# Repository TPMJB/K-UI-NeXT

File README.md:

# K-UI native VMU checkpoint: 74958b387827

This is a preservation checkpoint on `checkpoint/native-vmu-20261024` in
`TPMJB/K-UI-NeXT`. It preserves the exact source tree and all 36 original
source commits through `74958b3878279fc916199a7cd330f7f17b036138`, matching
compiled builds, generated test evidence, and the recovered EDF reference.
The checkpoint container is a separate Git commit; its own SHA is not the
original source SHA. This checkpoint does not merge changes into `main`.

## Compiled builds

- [Latest Background fallback limit, 74958b387827](builds/K-UI-Native-Background-Bounds-74958b387827.zip?raw=true).
- [Previous Standard and Background comparison build, 9fa65fc1cae0](builds/K-UI-VMU-Retry-9fa65fc1cae0.zip?raw=true).

The latest candidate retains background DMA and limits synchronous PIO fallback
to one SD data block per native loader call or reader interrupt. Tests
reproduced the previous whole-request masked-work defect and verified bounded
fallback, byte-exact completion, CRC recovery, guest DMA ownership and unchanged
DMA-only scheduling sequences. The linked memory and stack checks pass without
relaxing boundaries. These results do not establish a console performance fix.

The prior test reported smooth Evolution 2 FMVs with Background, with occasional
gameplay stalls. The latest report after the 74958b387827 candidate likewise
says FMVs remain fine but gameplay hangs remain. The build association follows
the delivery/test sequence; no runtime build screen was supplied with that
report. The gameplay performance problem is still open. See `HARDWARE-TESTS.json`.
The prior build is preserved for direct comparison. The user's earlier
flawless EDF FMV report used **regular Standard loading**, not Background.
The original regular-loading performance difference remains unresolved.

Follow the README inside the selected build ZIP to personalize its loader with
an existing prepared card profile. The latest package requires Background On;
it does not add a new in-game mode switch. Virtual A2 and physical A1 passthrough
remain included. This recovery script is not a device installer.

## Exact source recovery

Clone this checkpoint branch and run the following from this folder:

```sh
python3 restore.py
```

The script validates all preserved files and part hashes, reconstructs the
base history bundle and exact historical EDF source archive, imports the
retained main prerequisite and original source bundles, then checks out the
exact latest source in `restored-source`. It refuses to replace an existing
source directory. The original source tree, 36-commit count and Git object
integrity are checked after recovery.

The main prerequisite `194a94483132c8dd30b0a21d7c20887c0e1eaed3` is retained as
the checkpoint container's parent, keeping shared Git objects reachable. The
base compact bundle preserves the exact prior 35 source commits. The small
incremental bundle adds the original latest commit without recreating authors,
dates or commit IDs.

Latest source tree: `0640a3f8bf9cc53dd8701ee751af95e936491867`.
All payload identities and file hashes are recorded in `checkpoint.json`.
The large standalone Full ZIPs are not duplicated here: their unique source,
history and historical reference payloads are preserved directly instead.

## Historical reference and audits

`reference/edf20f0f11a3` preserves the exact recovered EDF module and source
archive. Its corrected `provenance.json` explicitly records regular loading.
`provenance-original.json` is an unchanged archival record whose earlier
Background interpretation is superseded; its payload identities remain valid.

`audit/edf/EDF-STANDARD-BINARY-AUDIT.md` describes the exact historical Standard
reconstruction and comparisons. The supplied corpus image's raw2352 format
does not establish which image variant was launched in either console test.
The safe reconstructed Standard ELF/bin/map are inspection evidence, not a
replacement loader package. Unsafe SCEV experiment executables are excluded.

`audit/background-bounds` records the reproduced defect, regression cases and
final linked checks. The work limit bounds PIO data blocks, not elapsed time;
legacy command/token/recovery waits remain. Preserved DMA-only scheduling does
not establish movie performance when a read itself falls back to PIO.

No user VMU image, save file, disk ownership profile, retail game executable or
game track is included. Original game files were used read-only for analysis
outside this checkpoint.

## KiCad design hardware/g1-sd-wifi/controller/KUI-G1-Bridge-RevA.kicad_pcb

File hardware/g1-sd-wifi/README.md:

# K-UI G1 microSD and Wi-Fi bridge — Rev A

The design now has a complete native KiCad circuit, two routed CN503 flex arms, selected components and original FPGA logic. All 55 BASE SMT part types have catalog matches (two LCSC codes were taken from a search index and must be confirmed on lcsc.com with their JLC SMT entries: C112291 for the 220 Ω FPGA configuration resistor added on 17 October, and C59873 for the TPS62172 converters that replaced TPS62162 on 23 October), and candidate BOM/CPL files exist. **Prototype fabrication is not released yet:** carrier routing and electrical layout review, mechanical support/fit and assembler placement/fixture review remain open. Device timing and firmware qualification are also outstanding. This directory supersedes the historical MCU-only starter.

The Dreamcast VA1 keeps its original 3.3 V GD-ROM as device0. The bridge supplies ATA device1, raw microSD sectors and Wi-Fi transport. K-UI is the sole filesystem owner; the C5 never independently mounts the card. exFAT is the baseline user choice; ext4 remains a software option. No FAT32 setup is prescribed.

| Implemented hardware | Selected component or circuit |
| --- | --- |
| ATA front end | U10 LCMXO2-2000HC-4TG100C; 50 MHz clock, JTAG configured by the RP2350 (J10 pads as an alternative), TX/RX FIFOs and hardware isolation |
| Controller | U201 RP2350B with boot NOR, native four-bit SD, USB/SWD recovery, and FPGA JTAG/PROGRAMn control |
| Bridge cache | U203 APS6404L-3SQR-ZR, 8 MiB PSRAM on QMI CS1/GPIO47; does not add SH-4 system RAM |
| microSD | Molex1040310811 socket, card detect, pullups and rail-qualified bidirectional isolation |
| Wi-Fi | Manual USB-free XIAO ESP32-C5, sixteen Harwin spring contacts, switched5 V, isolated SPI/UART and EN/BOOT recovery |
| Power | Dedicated fused 5 V pair (reverse-blocked on the bench only; installed, the tap-end harness fuse is the reverse-polarity protection), separate TPS62172 logic/storage bucks, power warning, supervisors and DNP reserve bank |
| G1 attachment | Independent passive20-conductor A/B arms and Hirose FH12 bottom-contact sockets; audio/+12 V excluded. The sockets must move before an order: arm B cannot reach J51 as placed |
| Optional BIOS | DNP x8 NOR, extra ROM taps, physical independent stock recovery and hardware-qualified write arm; active factory bank0 |

## Open the actual design

Open [the controller project](controller/KUI-G1-Bridge-RevA.kicad_pro) with KiCad10. The [root schematic](controller/KUI-G1-Bridge-RevA.kicad_sch) links eleven component sheets. The [carrier PCB](controller/KUI-G1-Bridge-RevA.kicad_pcb) is a draft with a BIOS clearance opening and an open CN503 notch. Both flex projects are under [flex/](flex/); A and B have different contact maps and are not interchangeable.

[Physical component contracts](design/blocks/) drive the deterministic schematic generator. Local symbol and footprint libraries are included. The [physical pad audit](design/physical-pad-audit.json) checks every electrical terminal against KiCad's loaded footprint, including exposed pads and connector anchors. [Controller notes](design/controller-implementation.md), [power/isolation notes](design/power-and-isolation.md) and [BIOS population notes](design/BIOS-variant.md) describe actual pins and circuits. [Current GPIO allocation](controller/K-UI-G1-GPIO-RevA.csv) is controller-to-FPGA/SD/C5, rather than the original direct-ATA candidate.

The reusable [integration checker](tools/check_integration.py) verifies the source contracts against the integrated native components and exported XML netlist, checks 100 FPGA package functions and 56 pin constraints, and evaluates 8,240 hardware safety combinations using the exported connections. From the repository root, run `python hardware/g1-sd-wifi/tools/check_integration.py --check`. After reviewed source changes and a fresh native netlist export, omit `--check` to refresh [integration-audit.json](design/integration-audit.json).

The [FPGA directory](fpga/) contains synthesizable logic, exact physical-pin LPF, simulation scoreboards and the MCU-link contract. Simulation and MachXO2 resource mapping pass. A Lattice device-fit/timing result and completed RP2350 ATA/media firmware are still required; there is no validated programming image or game-compatibility claim. Initial firmware must advertise PIO0 only. DMA ownership is provisioned and tested in simulation, but performance and physical timing are unqualified.

## Measured mechanical limits

One more console-open session is needed before the carrier or either flex arm is ordered: the unpowered CN503 row proof, the 1:1 fit check, the flex route survey and the shield-height check in [docs/OWNER-NEXT-STEPS.md](docs/OWNER-NEXT-STEPS.md) items 1, 3, 3a and 3b. Their results feed one more layout revision: the flex sockets J50/J51 must move, because arm B cannot reach J51 as placed. Motherboard-top clearance is6 mm in the BIOS/CN503/lower-shield region,8 mm elsewhere, and zero over the two thermal-contact chips. Nominal carrier underside is2.5 mm above the motherboard;0.8 mm PCB puts its top at3.3 mm. A2 mm FPC connector reaches5.3 mm before tolerances. The C5 assembly is reserved for the8 mm region and needs a supported0.90 mm contact gap and removable clamp.

BIOS body26.68 ×12.65 mm, outer lead span16.66 mm, height approximately2 mm. Its long axis is west-east; CN503's long axis is north-south. CN503 is38.67 mm long,6.56 mm maximum housing width; accepted solder-contact pitch is1.00 mm with approximately0.44 mm metal width. The25-contact measured run is24.39 mm. BIOS-to-connector housing distance is approximately12 mm; the west BIOS strip and east connector strip are approximately7 mm each. Those strips contain existing parts and solder joints. The housing-derived5.03 mm row spacing does not constrain the independent flex arms.

The 59 × 115 mm carrier envelope and cutout/notch north-south registration are provisional. The outline was 59 × 105 mm until 10 October 2026; it gained a 10 mm band between the FPGA area and the BIOS opening, so relative to the BIOS and CN503 the carrier now reaches 10 mm further north (toward the AV connector) and its south edge is unchanged. The angled photographs do not establish a production outline or support location. Existing tall capacitors, case features, thermal-pad pressure, C5 height/retention, SD access and shield insulation require mechanical review. No shield cutting is assumed. [Actual-size carrier fit sheets](mechanical/README.md) use native PCB edges and component pads, with Letter/A4 paper choices and independent horizontal/vertical calibration.

## Manufacture and review

[Manufacturing status](manufacturing/README.md) identifies the current order blockers, native checks, exact draft settings and procurement work. Final release uses three separate archives: rigid carrier, flexA and flexB. The exporter refuses to publish an order package while required checks, assembly data and reviewed source hashes are incomplete.

JLC's exact catalog pages require assembly support fixtures for both the **Harwin S7221-45R contacts (C22445132)** and **Abracon ASE-50.000MHZ-LC-T oscillator (C596955)**. Obtain assembler agreement on those fixtures before releasing an assembly order. The C5 retention clamp is a separate mechanical installation requirement. [The purchasing worksheet](manufacturing/parts-to-buy.csv) records the exact SMT identities and fixture notices.

The historical dispositions remain in [docs/](docs/); Claude's original reviews are pinned to [commit b207dd6](https://github.com/TPMJB/K-UI-NeXT/tree/b207dd659565826ffd757ccf7abe1998f63c9202/docs). The [implementation status](design/IMPLEMENTATION-STATUS-2026-10-10.md) maps each accepted addition to its circuit or source artifact and remaining condition. Software caching/OTA/BIOS programming, runtime bank switching and measured SD power-cut retention are subsequent implementation/qualification work; a DNP reserve capacitor footprint cannot establish safe write completion. The original controller starter is preserved under [controller/reference/](controller/reference/).

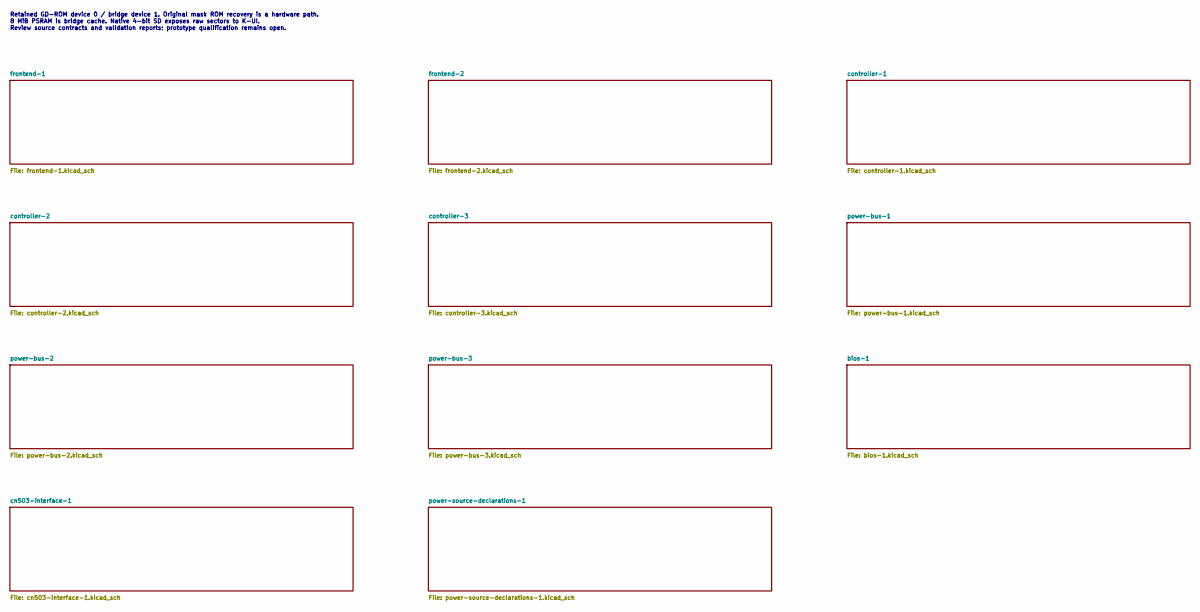
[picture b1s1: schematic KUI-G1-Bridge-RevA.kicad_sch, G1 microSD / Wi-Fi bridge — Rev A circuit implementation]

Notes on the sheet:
Retained GD-ROM device 0 / bridge device 1. Original mask ROM recovery is a hardware path. 8 MiB PSRAM is bridge cache. Native 4-bit SD exposes raw sectors to K-UI. Review source contracts and validation reports; prototype qualification remains open.

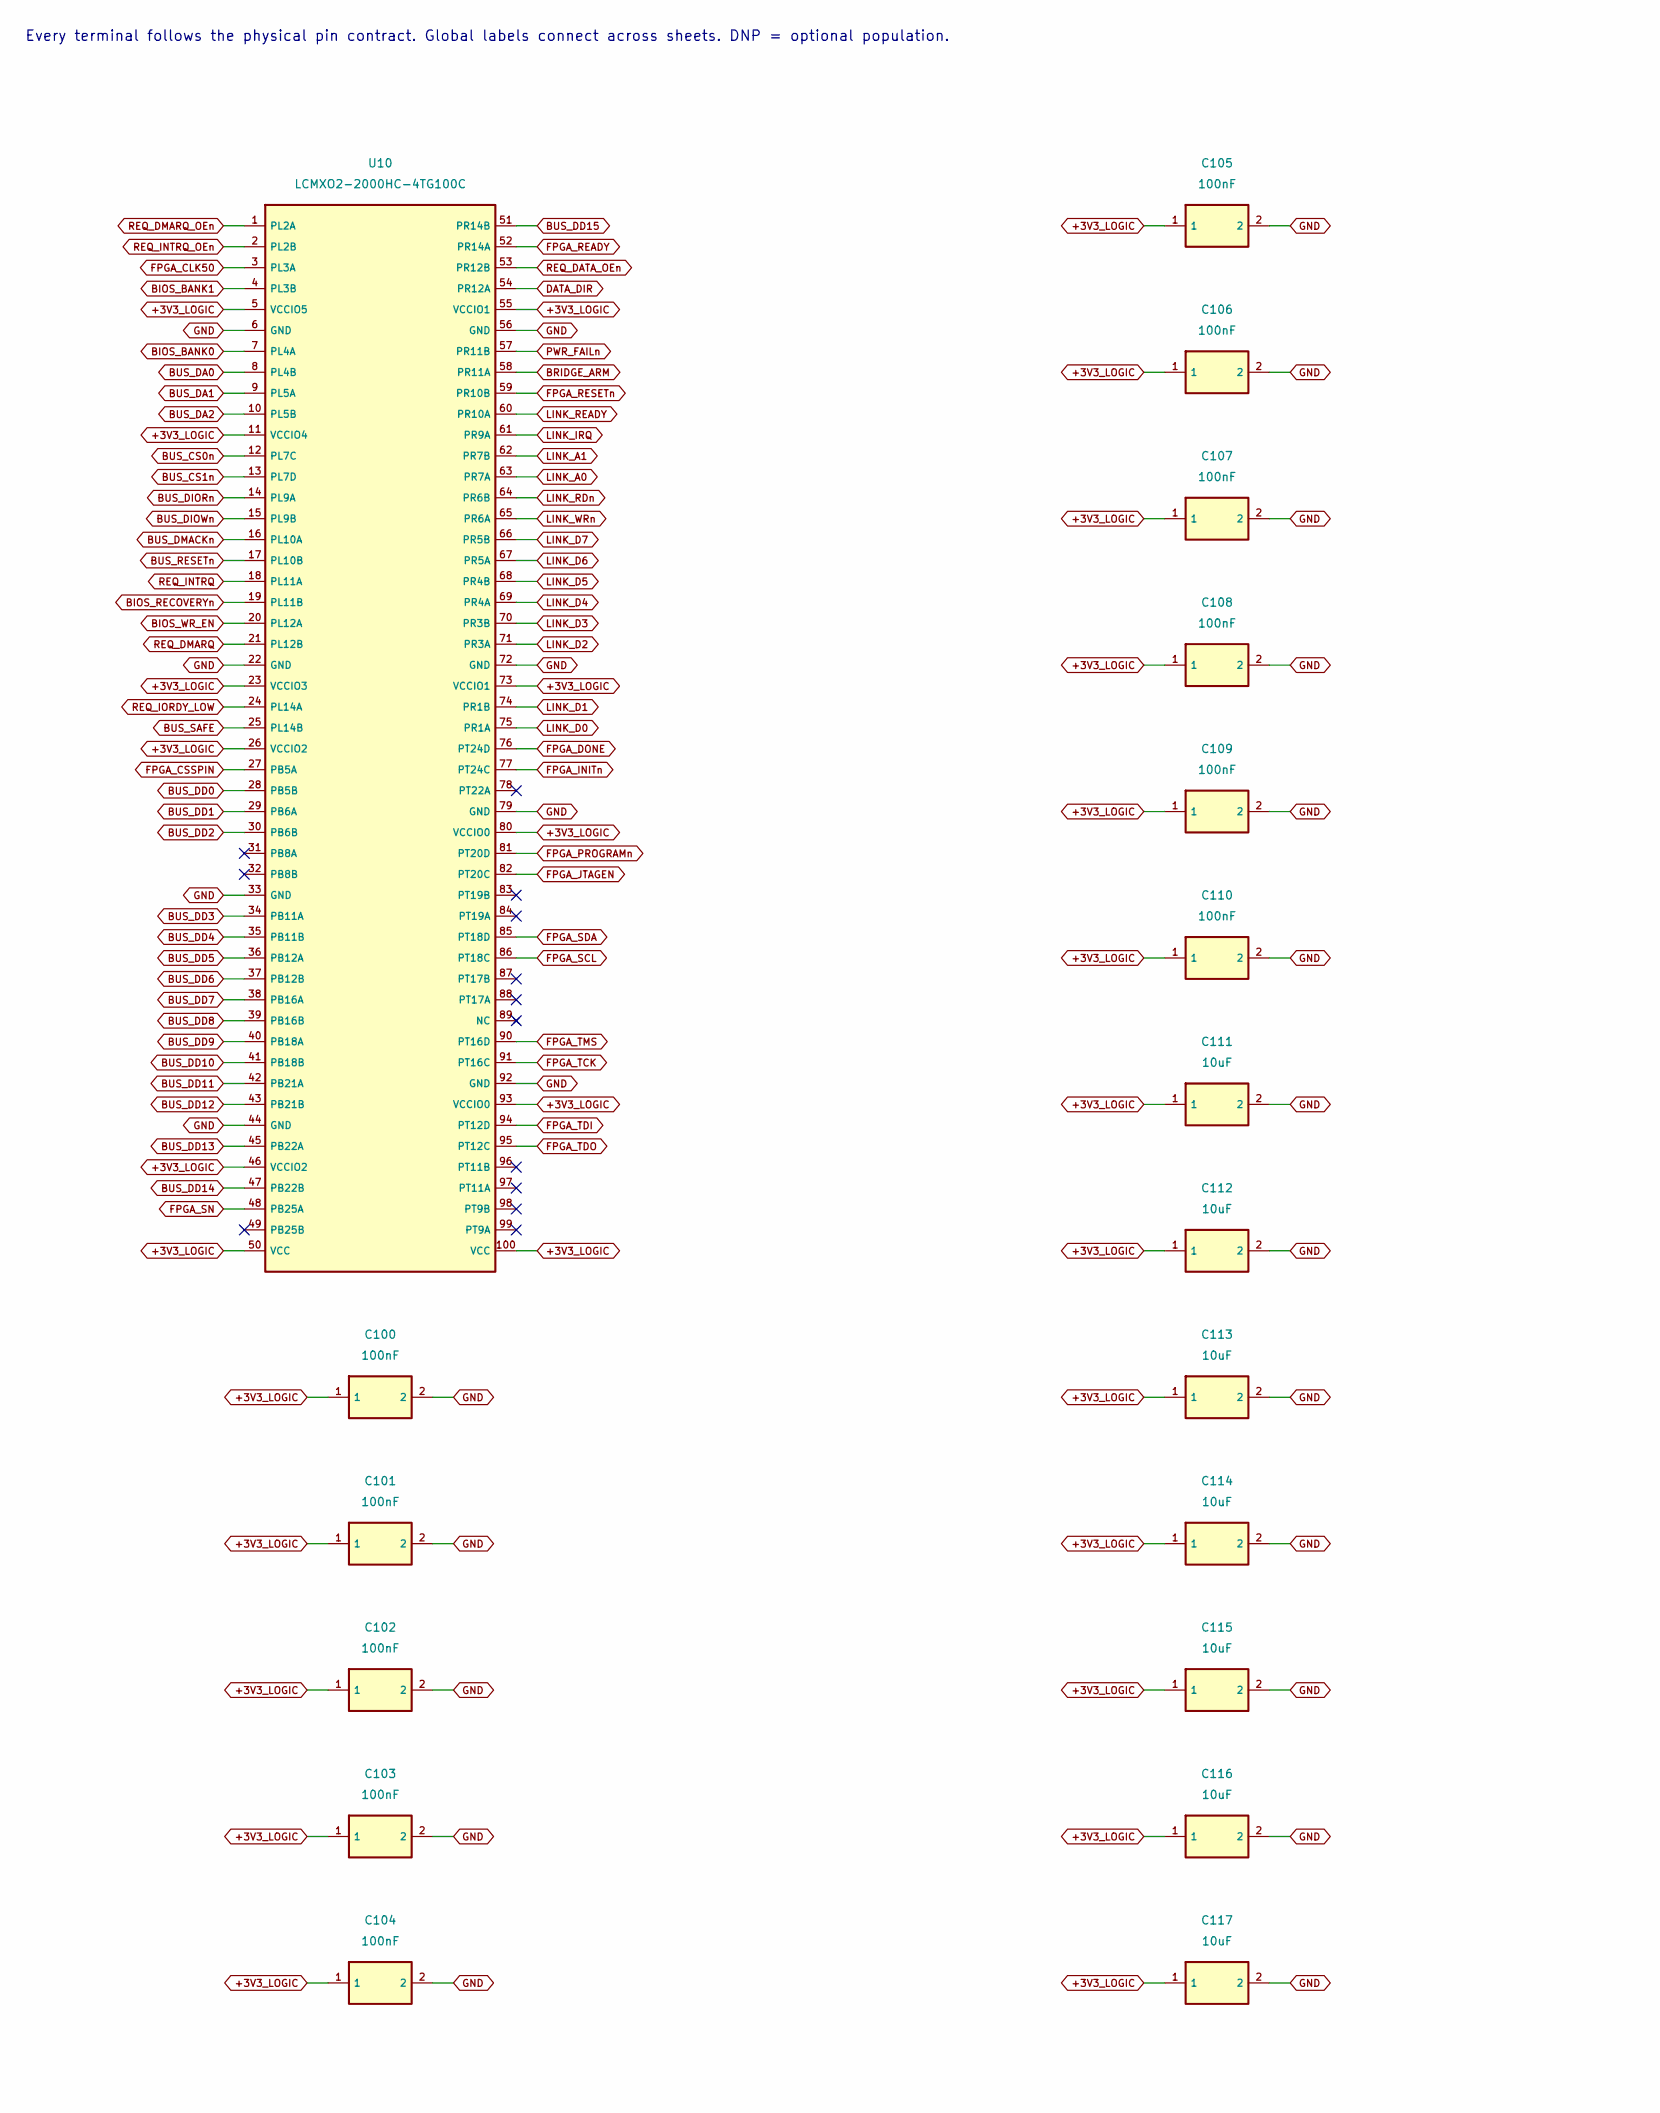
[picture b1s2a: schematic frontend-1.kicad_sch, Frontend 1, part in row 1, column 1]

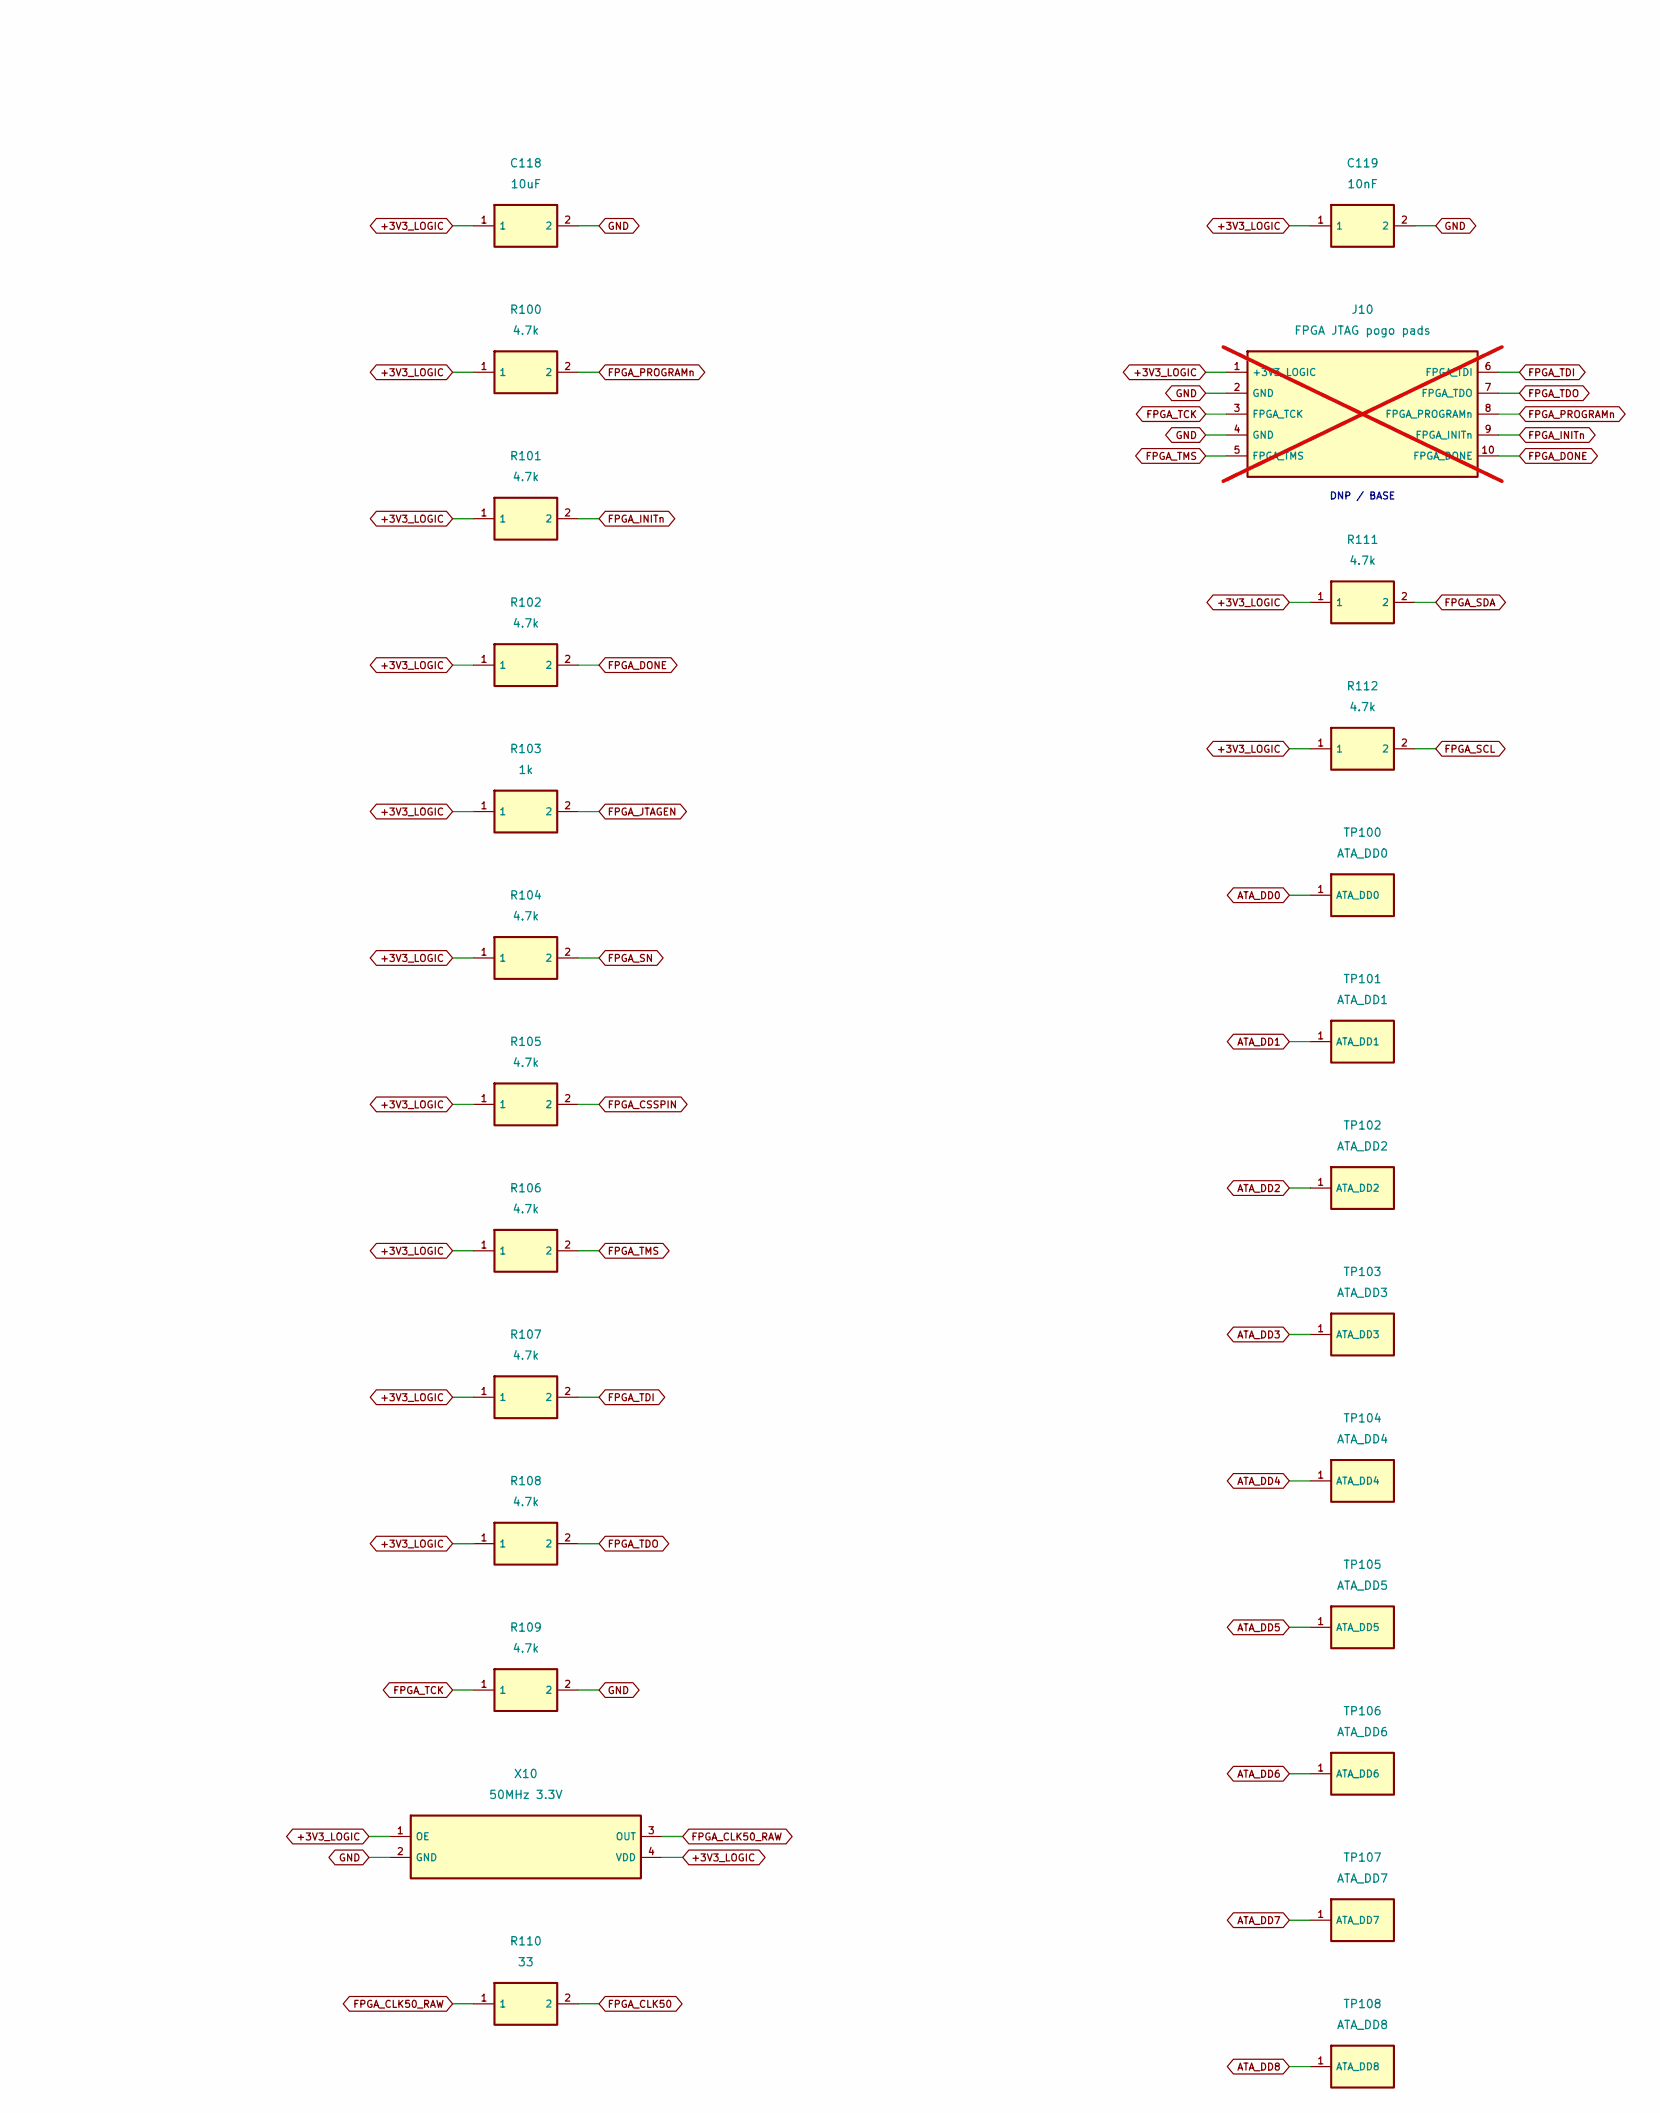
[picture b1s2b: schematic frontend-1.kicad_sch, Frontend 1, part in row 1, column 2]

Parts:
C100, C101, C102, C103, C104, C105, C106, C107, C108, C109, C110: 100nF; C_0402_1005Metric; MPN CL05B104KO5NNNC
C111, C112, C113, C114, C115, C116, C117, C118: 10uF; C_0603_1608Metric; MPN CL10A106MQ8NNNC
C119: 10nF; C_0402_1005Metric; MPN CL05B103KB5NNNC
J10: FPGA JTAG pogo pads; PinHeader_2x05_P1.27mm_Vertical; not fitted
R100, R101, R102, R104, R105, R106, R107, R108, R109, R111, R112: 4.7k; R_0402_1005Metric; MPN RC0402FR-074K7L
R103: 1k; R_0402_1005Metric; MPN RC0402FR-071KL
R110: 33; R_0402_1005Metric; MPN RC0402FR-0733RL
TP100: ATA_DD0; RawProbe_Pad_D1.0mm_NoPaste; MPN PCB_TEST_PAD
TP101: ATA_DD1; RawProbe_Pad_D1.0mm_NoPaste; MPN PCB_TEST_PAD
TP102: ATA_DD2; RawProbe_Pad_D1.0mm_NoPaste; MPN PCB_TEST_PAD
TP103: ATA_DD3; RawProbe_Pad_D1.0mm_NoPaste; MPN PCB_TEST_PAD
TP104: ATA_DD4; RawProbe_Pad_D1.0mm_NoPaste; MPN PCB_TEST_PAD
TP105: ATA_DD5; RawProbe_Pad_D1.0mm_NoPaste; MPN PCB_TEST_PAD
TP106: ATA_DD6; RawProbe_Pad_D1.0mm_NoPaste; MPN PCB_TEST_PAD
TP107: ATA_DD7; RawProbe_Pad_D1.0mm_NoPaste; MPN PCB_TEST_PAD
TP108: ATA_DD8; RawProbe_Pad_D1.0mm_NoPaste; MPN PCB_TEST_PAD
U10: LCMXO2-2000HC-4TG100C; TQFP-100_14x14mm_P0.5mm; MPN LCMXO2-2000HC-4TG100C; LCSC C1521632
X10: 50MHz 3.3V; Oscillator_SMD_Abracon_ASE-4Pin_3.2x2.5mm; MPN ASE-50.000MHZ-LC-T

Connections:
+3V3_LOGIC: C100.1, C101.1, C102.1, C103.1, C104.1, C105.1, C106.1, C107.1, C108.1, C109.1, C110.1, C111.1, C112.1, C113.1, C114.1, C115.1, C116.1, C117.1, C118.1, C119.1, J10.1 (+3V3_LOGIC), R100.1, R101.1, R102.1, R103.1, R104.1, R105.1, R106.1, R107.1, R108.1, R111.1, R112.1, U10.5 (VCCIO5), U10.11 (VCCIO4), U10.23 (VCCIO3), U10.26 (VCCIO2), U10.46 (VCCIO2), U10.50 (VCC), U10.55 (VCCIO1), U10.73 (VCCIO1), U10.80 (VCCIO0), U10.93 (VCCIO0), U10.100 (VCC), X10.1 (OE), X10.4 (VDD); also elsewhere on the board
ATA_DD0: TP100.1; also elsewhere on the board
ATA_DD1: TP101.1; also elsewhere on the board
ATA_DD2: TP102.1; also elsewhere on the board
ATA_DD3: TP103.1; also elsewhere on the board
ATA_DD4: TP104.1; also elsewhere on the board
ATA_DD5: TP105.1; also elsewhere on the board
ATA_DD6: TP106.1; also elsewhere on the board
ATA_DD7: TP107.1; also elsewhere on the board
ATA_DD8: TP108.1; also elsewhere on the board
BIOS_BANK0: U10.7 (PL4A); also elsewhere on the board
BIOS_BANK1: U10.4 (PL3B); also elsewhere on the board
BIOS_RECOVERYn: U10.19 (PL11B); also elsewhere on the board
BIOS_WR_EN: U10.20 (PL12A); also elsewhere on the board
BRIDGE_ARM: U10.58 (PR11A); also elsewhere on the board
BUS_CS0n: U10.12 (PL7C); also elsewhere on the board
BUS_CS1n: U10.13 (PL7D); also elsewhere on the board
BUS_DA0: U10.8 (PL4B); also elsewhere on the board
BUS_DA1: U10.9 (PL5A); also elsewhere on the board
BUS_DA2: U10.10 (PL5B); also elsewhere on the board
BUS_DD0: U10.28 (PB5B); also elsewhere on the board
BUS_DD1: U10.29 (PB6A); also elsewhere on the board
BUS_DD2: U10.30 (PB6B); also elsewhere on the board
BUS_DD3: U10.34 (PB11A); also elsewhere on the board
BUS_DD4: U10.35 (PB11B); also elsewhere on the board
BUS_DD5: U10.36 (PB12A); also elsewhere on the board
BUS_DD6: U10.37 (PB12B); also elsewhere on the board
BUS_DD7: U10.38 (PB16A); also elsewhere on the board
BUS_DD8: U10.39 (PB16B); also elsewhere on the board
BUS_DD9: U10.40 (PB18A); also elsewhere on the board
BUS_DD10: U10.41 (PB18B); also elsewhere on the board
BUS_DD11: U10.42 (PB21A); also elsewhere on the board
BUS_DD12: U10.43 (PB21B); also elsewhere on the board
BUS_DD13: U10.45 (PB22A); also elsewhere on the board
BUS_DD14: U10.47 (PB22B); also elsewhere on the board
BUS_DD15: U10.51 (PR14B); also elsewhere on the board
BUS_DIORn: U10.14 (PL9A); also elsewhere on the board
BUS_DIOWn: U10.15 (PL9B); also elsewhere on the board
BUS_DMACKn: U10.16 (PL10A); also elsewhere on the board
BUS_RESETn: U10.17 (PL10B); also elsewhere on the board
BUS_SAFE: U10.25 (PL14B); also elsewhere on the board
DATA_DIR: U10.54 (PR12A); also elsewhere on the board
FPGA_CLK50: R110.2, U10.3 (PL3A)
FPGA_CLK50_RAW: R110.1, X10.3 (OUT)
FPGA_CSSPIN: R105.2, U10.27 (PB5A)
FPGA_DONE: J10.10 (FPGA_DONE), R102.2, U10.76 (PT24D)
FPGA_INITn: J10.9 (FPGA_INITn), R101.2, U10.77 (PT24C)
FPGA_JTAGEN: R103.2, U10.82 (PT20C)
FPGA_PROGRAMn: J10.8 (FPGA_PROGRAMn), R100.2, U10.81 (PT20D); also elsewhere on the board
FPGA_READY: U10.52 (PR14A); also elsewhere on the board
FPGA_RESETn: U10.59 (PR10B); also elsewhere on the board
FPGA_SCL: R112.2, U10.86 (PT18C)
FPGA_SDA: R111.2, U10.85 (PT18D)
FPGA_SN: R104.2, U10.48 (PB25A)
FPGA_TCK: J10.3 (FPGA_TCK), R109.1, U10.91 (PT16C); also elsewhere on the board
FPGA_TDI: J10.6 (FPGA_TDI), R107.2, U10.94 (PT12D); also elsewhere on the board
FPGA_TDO: J10.7 (FPGA_TDO), R108.2, U10.95 (PT12C); also elsewhere on the board
FPGA_TMS: J10.5 (FPGA_TMS), R106.2, U10.90 (PT16D); also elsewhere on the board
GND: C100.2, C101.2, C102.2, C103.2, C104.2, C105.2, C106.2, C107.2, C108.2, C109.2, C110.2, C111.2, C112.2, C113.2, C114.2, C115.2, C116.2, C117.2, C118.2, C119.2, J10.2 (GND), J10.4 (GND), R109.2, U10.6 (GND), U10.22 (GND), U10.33 (GND), U10.44 (GND), U10.56 (GND), U10.72 (GND), U10.79 (GND), U10.92 (GND), X10.2 (GND); also elsewhere on the board
LINK_A0: U10.63 (PR7A); also elsewhere on the board
LINK_A1: U10.62 (PR7B); also elsewhere on the board
LINK_D0: U10.75 (PR1A); also elsewhere on the board
LINK_D1: U10.74 (PR1B); also elsewhere on the board
LINK_D2: U10.71 (PR3A); also elsewhere on the board
LINK_D3: U10.70 (PR3B); also elsewhere on the board
LINK_D4: U10.69 (PR4A); also elsewhere on the board
LINK_D5: U10.68 (PR4B); also elsewhere on the board
LINK_D6: U10.67 (PR5A); also elsewhere on the board
LINK_D7: U10.66 (PR5B); also elsewhere on the board
LINK_IRQ: U10.61 (PR9A); also elsewhere on the board
LINK_RDn: U10.64 (PR6B); also elsewhere on the board
LINK_READY: U10.60 (PR10A); also elsewhere on the board
LINK_WRn: U10.65 (PR6A); also elsewhere on the board
PWR_FAILn: U10.57 (PR11B); also elsewhere on the board
REQ_DATA_OEn: U10.53 (PR12B); also elsewhere on the board
REQ_DMARQ: U10.21 (PL12B); also elsewhere on the board
REQ_DMARQ_OEn: U10.1 (PL2A); also elsewhere on the board
REQ_INTRQ: U10.18 (PL11A); also elsewhere on the board
REQ_INTRQ_OEn: U10.2 (PL2B); also elsewhere on the board
REQ_IORDY_LOW: U10.24 (PL14A); also elsewhere on the board

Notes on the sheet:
Every terminal follows the physical pin contract. Global labels connect across sheets. DNP = optional population.
DNP / BASE

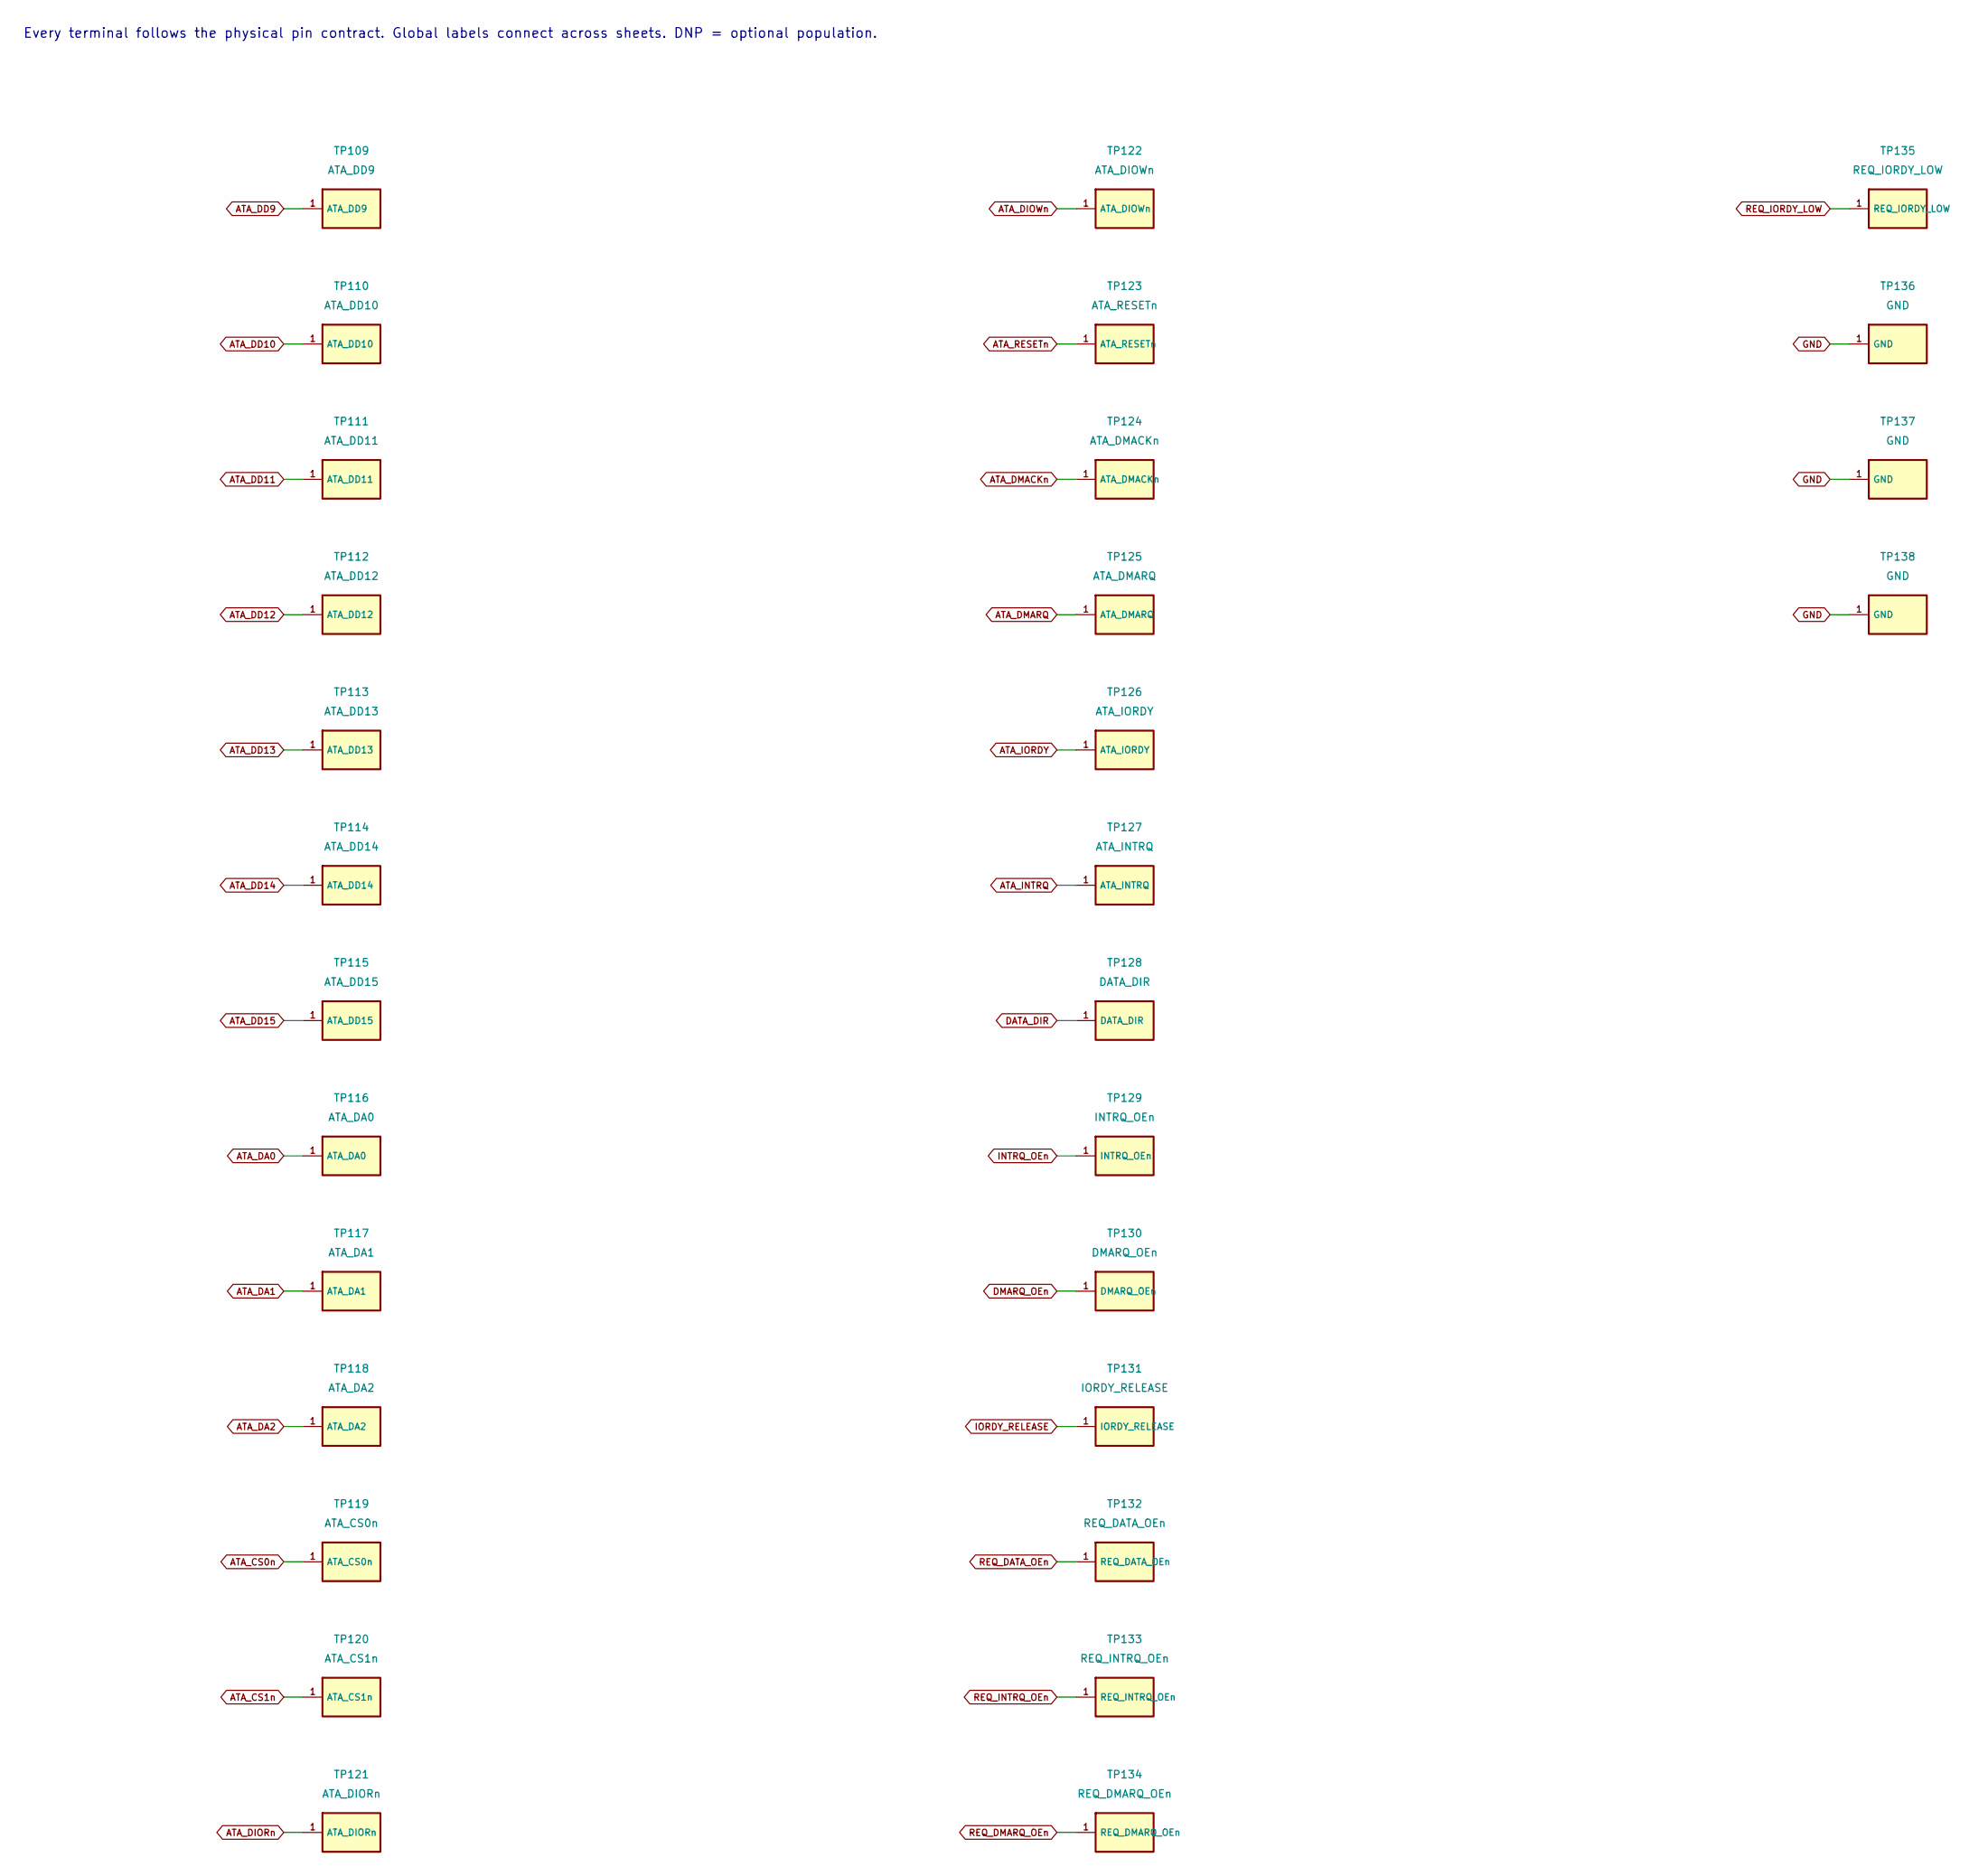
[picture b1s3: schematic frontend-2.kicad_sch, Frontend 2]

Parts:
TP109: ATA_DD9; RawProbe_Pad_D1.0mm_NoPaste; MPN PCB_TEST_PAD
TP110: ATA_DD10; RawProbe_Pad_D1.0mm_NoPaste; MPN PCB_TEST_PAD
TP111: ATA_DD11; RawProbe_Pad_D1.0mm_NoPaste; MPN PCB_TEST_PAD
TP112: ATA_DD12; RawProbe_Pad_D1.0mm_NoPaste; MPN PCB_TEST_PAD
TP113: ATA_DD13; RawProbe_Pad_D1.0mm_NoPaste; MPN PCB_TEST_PAD
TP114: ATA_DD14; RawProbe_Pad_D1.0mm_NoPaste; MPN PCB_TEST_PAD
TP115: ATA_DD15; RawProbe_Pad_D1.0mm_NoPaste; MPN PCB_TEST_PAD
TP116: ATA_DA0; RawProbe_Pad_D1.0mm_NoPaste; MPN PCB_TEST_PAD
TP117: ATA_DA1; RawProbe_Pad_D1.0mm_NoPaste; MPN PCB_TEST_PAD
TP118: ATA_DA2; RawProbe_Pad_D1.0mm_NoPaste; MPN PCB_TEST_PAD
TP119: ATA_CS0n; RawProbe_Pad_D1.0mm_NoPaste; MPN PCB_TEST_PAD
TP120: ATA_CS1n; RawProbe_Pad_D1.0mm_NoPaste; MPN PCB_TEST_PAD
TP121: ATA_DIORn; RawProbe_Pad_D1.0mm_NoPaste; MPN PCB_TEST_PAD
TP122: ATA_DIOWn; RawProbe_Pad_D1.0mm_NoPaste; MPN PCB_TEST_PAD
TP123: ATA_RESETn; RawProbe_Pad_D1.0mm_NoPaste; MPN PCB_TEST_PAD
TP124: ATA_DMACKn; RawProbe_Pad_D1.0mm_NoPaste; MPN PCB_TEST_PAD
TP125: ATA_DMARQ; RawProbe_Pad_D1.0mm_NoPaste; MPN PCB_TEST_PAD
TP126: ATA_IORDY; RawProbe_Pad_D1.0mm_NoPaste; MPN PCB_TEST_PAD
TP127: ATA_INTRQ; RawProbe_Pad_D1.0mm_NoPaste; MPN PCB_TEST_PAD
TP128: DATA_DIR; RawProbe_Pad_D1.0mm_NoPaste; MPN PCB_TEST_PAD
TP129: INTRQ_OEn; RawProbe_Pad_D1.0mm_NoPaste; MPN PCB_TEST_PAD
TP130: DMARQ_OEn; RawProbe_Pad_D1.0mm_NoPaste; MPN PCB_TEST_PAD
TP131: IORDY_RELEASE; RawProbe_Pad_D1.0mm_NoPaste; MPN PCB_TEST_PAD
TP132: REQ_DATA_OEn; RawProbe_Pad_D1.0mm_NoPaste; MPN PCB_TEST_PAD
TP133: REQ_INTRQ_OEn; RawProbe_Pad_D1.0mm_NoPaste; MPN PCB_TEST_PAD
TP134: REQ_DMARQ_OEn; RawProbe_Pad_D1.0mm_NoPaste; MPN PCB_TEST_PAD
TP135: REQ_IORDY_LOW; RawProbe_Pad_D1.0mm_NoPaste; MPN PCB_TEST_PAD
TP136, TP137, TP138: GND; RawProbe_Pad_D1.0mm_NoPaste; MPN PCB_TEST_PAD

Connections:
ATA_CS0n: TP119.1; also elsewhere on the board
ATA_CS1n: TP120.1; also elsewhere on the board
ATA_DA0: TP116.1; also elsewhere on the board
ATA_DA1: TP117.1; also elsewhere on the board
ATA_DA2: TP118.1; also elsewhere on the board
ATA_DD9: TP109.1; also elsewhere on the board
ATA_DD10: TP110.1; also elsewhere on the board
ATA_DD11: TP111.1; also elsewhere on the board
ATA_DD12: TP112.1; also elsewhere on the board
ATA_DD13: TP113.1; also elsewhere on the board
ATA_DD14: TP114.1; also elsewhere on the board
ATA_DD15: TP115.1; also elsewhere on the board
ATA_DIORn: TP121.1; also elsewhere on the board
ATA_DIOWn: TP122.1; also elsewhere on the board
ATA_DMACKn: TP124.1; also elsewhere on the board
ATA_DMARQ: TP125.1; also elsewhere on the board
ATA_INTRQ: TP127.1; also elsewhere on the board
ATA_IORDY: TP126.1; also elsewhere on the board
ATA_RESETn: TP123.1; also elsewhere on the board
DATA_DIR: TP128.1; also elsewhere on the board
DMARQ_OEn: TP130.1; also elsewhere on the board
GND: TP136.1, TP137.1, TP138.1; also elsewhere on the board
INTRQ_OEn: TP129.1; also elsewhere on the board
IORDY_RELEASE: TP131.1; also elsewhere on the board
REQ_DATA_OEn: TP132.1; also elsewhere on the board
REQ_DMARQ_OEn: TP134.1; also elsewhere on the board
REQ_INTRQ_OEn: TP133.1; also elsewhere on the board
REQ_IORDY_LOW: TP135.1; also elsewhere on the board

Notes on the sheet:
Every terminal follows the physical pin contract. Global labels connect across sheets. DNP = optional population.
